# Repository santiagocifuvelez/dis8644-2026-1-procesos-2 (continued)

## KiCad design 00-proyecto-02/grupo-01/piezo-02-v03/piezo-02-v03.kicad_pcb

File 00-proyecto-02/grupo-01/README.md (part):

# proyecto-02

## Grupo

Número de grupo: 01

Tema del grupo: Piezo

Integrantes:

- Benjamín Alonso Álvarez Pavez / [benjaminalvarez21](<https://github.com/disenoUDP/dis8644-2026-1-procesos-2/tree/main/03-benjaminalvarez21>)
- Anays Valentina Cornejo Candia / [Anaysval](<https://github.com/disenoUDP/dis8644-2026-1-procesos-2/tree/main/09-Anaysval>)
- Bruno Ferrari Meyer / [chknngttts](<https://github.com/disenoUDP/dis8644-2026-1-procesos-2/tree/main/11-chknngttts>)
- Lucas Ignacio Ortiz Aguirre / [ryukivol](<https://github.com/disenoUDP/dis8644-2026-1-procesos-2/tree/main/21-ryukivol>)
- Nicolás Elías Valdés Greve / [nicolasvaldesgreve](<https://github.com/disenoUDP/dis8644-2026-1-procesos-2/tree/main/31-nicolasvaldesgreve>)

## Circuito 1

maincra

### Descripción general/conceptual 1

Este módulo te permite interactuar con el sintetizador mediante vibraciones en el piezo, tales como golpes en la misma superficie en la que se encuentra el componente o utilizándolo en nuestro cuerpo y causar vibraciones con nuestra garganta. Estas vibraciones serás captadas por el piezo, lo cual lo tomará como señal para avanzar en el secuenciador.

La idea detrás de esta propuesta nace de la posibilidad de sentir y ver las vibraciones. Aquello que parece caótico o insignificante puede contener señales que, al prestar suficiente atención, adquieren un significado propio. Siguiendo esa lógica, el piezo actúa como un medio para captar esas pequeñas vibraciones y convertirlas en acciones dentro del sintetizador, permitiendo que elementos normalmente invisibles se vuelvan parte de la interacción.

### Descripción de funcionamiento 1

El circuito se conforma de 7 partes:
  - Piezoeléctrico
  - Pre-Amp (TL072)
  - Inversor de señal (2N2222)
  - Regulador de voltaje (L7805CV)
  - Filtro Low-pass
  - Clock (NE555P)
  - Secuenciador (CD4017)

Como estándar en el trabajo todos tenemos que alimentar nuestro circuito con 5V. Para esto usamos el L7805CV

El piezo tiene 3 estados al recibir señal.

Para que el Pre-Amp pueda recibir la señal correctamente se necesita crear un voltaje medio entre VCC y GND. Para esto se usan 2 Resistencias del mismo valor, que dividen el voltaje a la mitad **``5V ---> 2.5V``**, esto permite que capte la señal completa y funcione correctamente. El Pre-Amp en nuestro caso también funciona para aumentar la sensibilidad del piezo, normalmente este solo detecta las señales directas al disco cerámico del piezo, pero con el Pre-Amp logramos que detecte señales a varios centímetros de este. 

Para afinar la señal que recibe el inversor, colocamos un filtro low-pass, esto permite que solo corriente bajo los 500hz *aprox.* avancen en el circuito. Esta señal entra al transistor (2N2222) que invierte la señal que recibe, puesto que el Clock (NE555P) busca recibir señales negativas en su Trigger [pin 2] para funcionar. El Clock en modo monoestable se conecta con el pin 14 del secuenciador (CD4017) para que señale cuando se avanza en los steps. 

### Descubrimientos

- Modificando los valores de las resistencias, se logra amplificar la sensibilidad del piezo (gracias misaaaaaa).
- Tener protoboard con los orificios **no** suelto es vital para que el circuito sea estable y se pueda mover.
- Que ciertos amplificadores tienen usos específicos, como el LM386 que es óptimo para parlantes, pero no piezos.
- Se pueden sustituir componentes con valores diferentes **``2.2k Ω ---> 47 Ω``**

### Esquemático 

### PCB 1

### Documentación audiovisual funcionamiento protoboard 1

[video-piezo-01](https://youtu.be/JZCzPmO_yxs)

### BOM

| Componente | Cantidad | Valor unitario | Link |
| --- | --- | --- | --- |
| Chip NE555P | 1 | $490 | <https://www.victronics.cl/circuitos-integrados/lm555cngeneralpurposebipolartimerdip8/> |
| Chip TL072CP | 1 | $990 | <https://www.victronics.cl/circuitos-integrados/tl072cpdualjfetlowpoweropamplifierdip8/> |
| Chip CD4017 | 1 | $890 | <https://www.mechatronicstore.cl/circuito-integrado-4017-contador/?srsltid=AfmBOopG29clQvJ0CqcNNp17wxEDjZ1w8dAWqRPMAcTqycciqYjHE40h>
| Regulador L7805CV | 1 | $350 | <https://www.victronics.cl/reguladores/reguladorvoltl7805cv5v-15ato220/> |
| Diodo 1N4007 | 1 | $200 | <https://www.mechatronicstore.cl/diodo-rectificador-in4007-1n4007-4007/> |
| Diodo BAT85 | 2 | $586 | <https://cl.rsdelivers.com/product/nexperia/bat85113/nexperia-diodo-bat85113-diodo-schottky-200-ma-30-v/0300978> |
| Transistor 2N2222 | 1 | $200 | <https://www.mechatronicstore.cl/transistor-2n2222/> |
| Potenciómetro B10K | 1 | $495 | <https://altronics.cl/potenciometro-lineal-10k-b10k> |
| Potenciómetro B500K | 1 | $495 | <https://altronics.cl/potenciometro-lineal-500k-b500k?search=b500k> |
| LED 3mm | 5 | $100 | <https://www.mechatronicstore.cl/led-3mm-5mm/> |
| Resistencia 47 Ω | 1 | $90 | <https://www.electroardu.cl/resistencias-1k-ohm?srsltid=AfmBOor81HKrzfoOTnLK3FU6ObPuf1EPUVMS0naCwqMNIzGt8LYDiUYt> |
| Resistencia 100 Ω | 1 | $90 | <https://www.electroardu.cl/resistencias-1k-ohm?srsltid=AfmBOor81HKrzfoOTnLK3FU6ObPuf1EPUVMS0naCwqMNIzGt8LYDiUYt> |
| Resistencia 220 Ω | 1 | $90 | <https://www.electroardu.cl/resistencias-1k-ohm?srsltid=AfmBOor81HKrzfoOTnLK3FU6ObPuf1EPUVMS0naCwqMNIzGt8LYDiUYt> |
| Resistencia 1 KΩ | 8 | $90 | <https://www.electroardu.cl/resistencias-1k-ohm?srsltid=AfmBOor81HKrzfoOTnLK3FU6ObPuf1EPUVMS0naCwqMNIzGt8LYDiUYt> |
| Resistencia 10 KΩ | 4 | $90 | <https://www.electroardu.cl/resistencias-1k-ohm?srsltid=AfmBOor81HKrzfoOTnLK3FU6ObPuf1EPUVMS0naCwqMNIzGt8LYDiUYt> |
| Resistencia 100 KΩ | 5 | $90 | <https://www.electroardu.cl/resistencias-1k-ohm?srsltid=AfmBOor81HKrzfoOTnLK3FU6ObPuf1EPUVMS0naCwqMNIzGt8LYDiUYt> |
| Condensador cerámico 4.7 nF | 1 | $100 | <https://www.mechatronicstore.cl/condensadores-ceramicos-distintos-valores/> |
| Condensador cerámico 10 nF | 1 | $100 | <https://www.mechatronicstore.cl/condensadores-ceramicos-distintos-valores/> |
| Condensador cerámico 100 nF | 4 | $100 | <https://www.mechatronicstore.cl/condensadores-ceramicos-distintos-valores/> |
| Condensador polarizado 10 µF | 2 | $100 | <https://www.mechatronicstore.cl/condensador-capacitorio-de-electrolitico-por-unidad-varios-valores/> |
| Condensador polarizado 100 µF | 3 | $100 | <https://www.mechatronicstore.cl/condensador-capacitorio-de-electrolitico-por-unidad-varios-valores/> | 
| Cables dupont 40 uni. | 1 | $2.990 | <https://mcielectronics.cl/shop/product/cable-dupont-macho-macho-20cm-pack-40-unidades-2/> |
| Cables caimán | 2 | $1.990 | <https://www.mechatronicstore.cl/cable-conector-cocodrilo-o-caiman-5-unidades/> |
| Batería 9V recargable | 1 | $7.990 | <https://www.sodimac.cl/sodimac-cl/articulo/110251085/bateria-recargable-9v/110251089> |
| Conector batería | 1 | $1.990 | <https://mcielectronics.cl/shop/product/conector-para-baterias-de-9v-9800/?srsltid=AfmBOorf4iqHmZZbBCSLCPoI-UFTBMuBMtXEwLw-ia48KteW5jir8sIx> |
| Piezo | 1 | $990 | <https://www.mechatronicstore.cl/sensor-piezoelectrico-27mm-con-cable/> |
| Interruptor Switch | 1 | $570 | <https://www.katode.cl/switches/1339-interruptor-switch-2-pines-on-off-corto.html?srsltid=AfmBOorJlIeUySzAORFwXSattHKE4BKH2LmhhXZS_8fZ4MW-G6kwnxqA> |

## Circuito 2

Budumtz

### Descripción general/conceptual 2

Este módulo, al igual que el anterior, permite que uno pueda interactuar con el sintetizador al que esté conectado el piezo, pero en este caso se necesita contacto directo al componente lo cual permitirá que lo que esté conectado a este se active.

El nombre surge de esos sonidos de batería cortos que suelen acompañar el remate de un chiste, donde un único golpe logra llamar la atención y marcar un momento específico.

De forma parecida, cada impacto sobre el piezo genera una respuesta inmediata en el circuito.

### Descripción de funcionamiento 2

El circuito se conforma por 5 partes:

+ Piezoeléctrico
+ High pass filter
+ Op-Amp (LM324)
+ Inversor de señal (2N2222)
+ Regulador de voltaje (L7805CV)

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
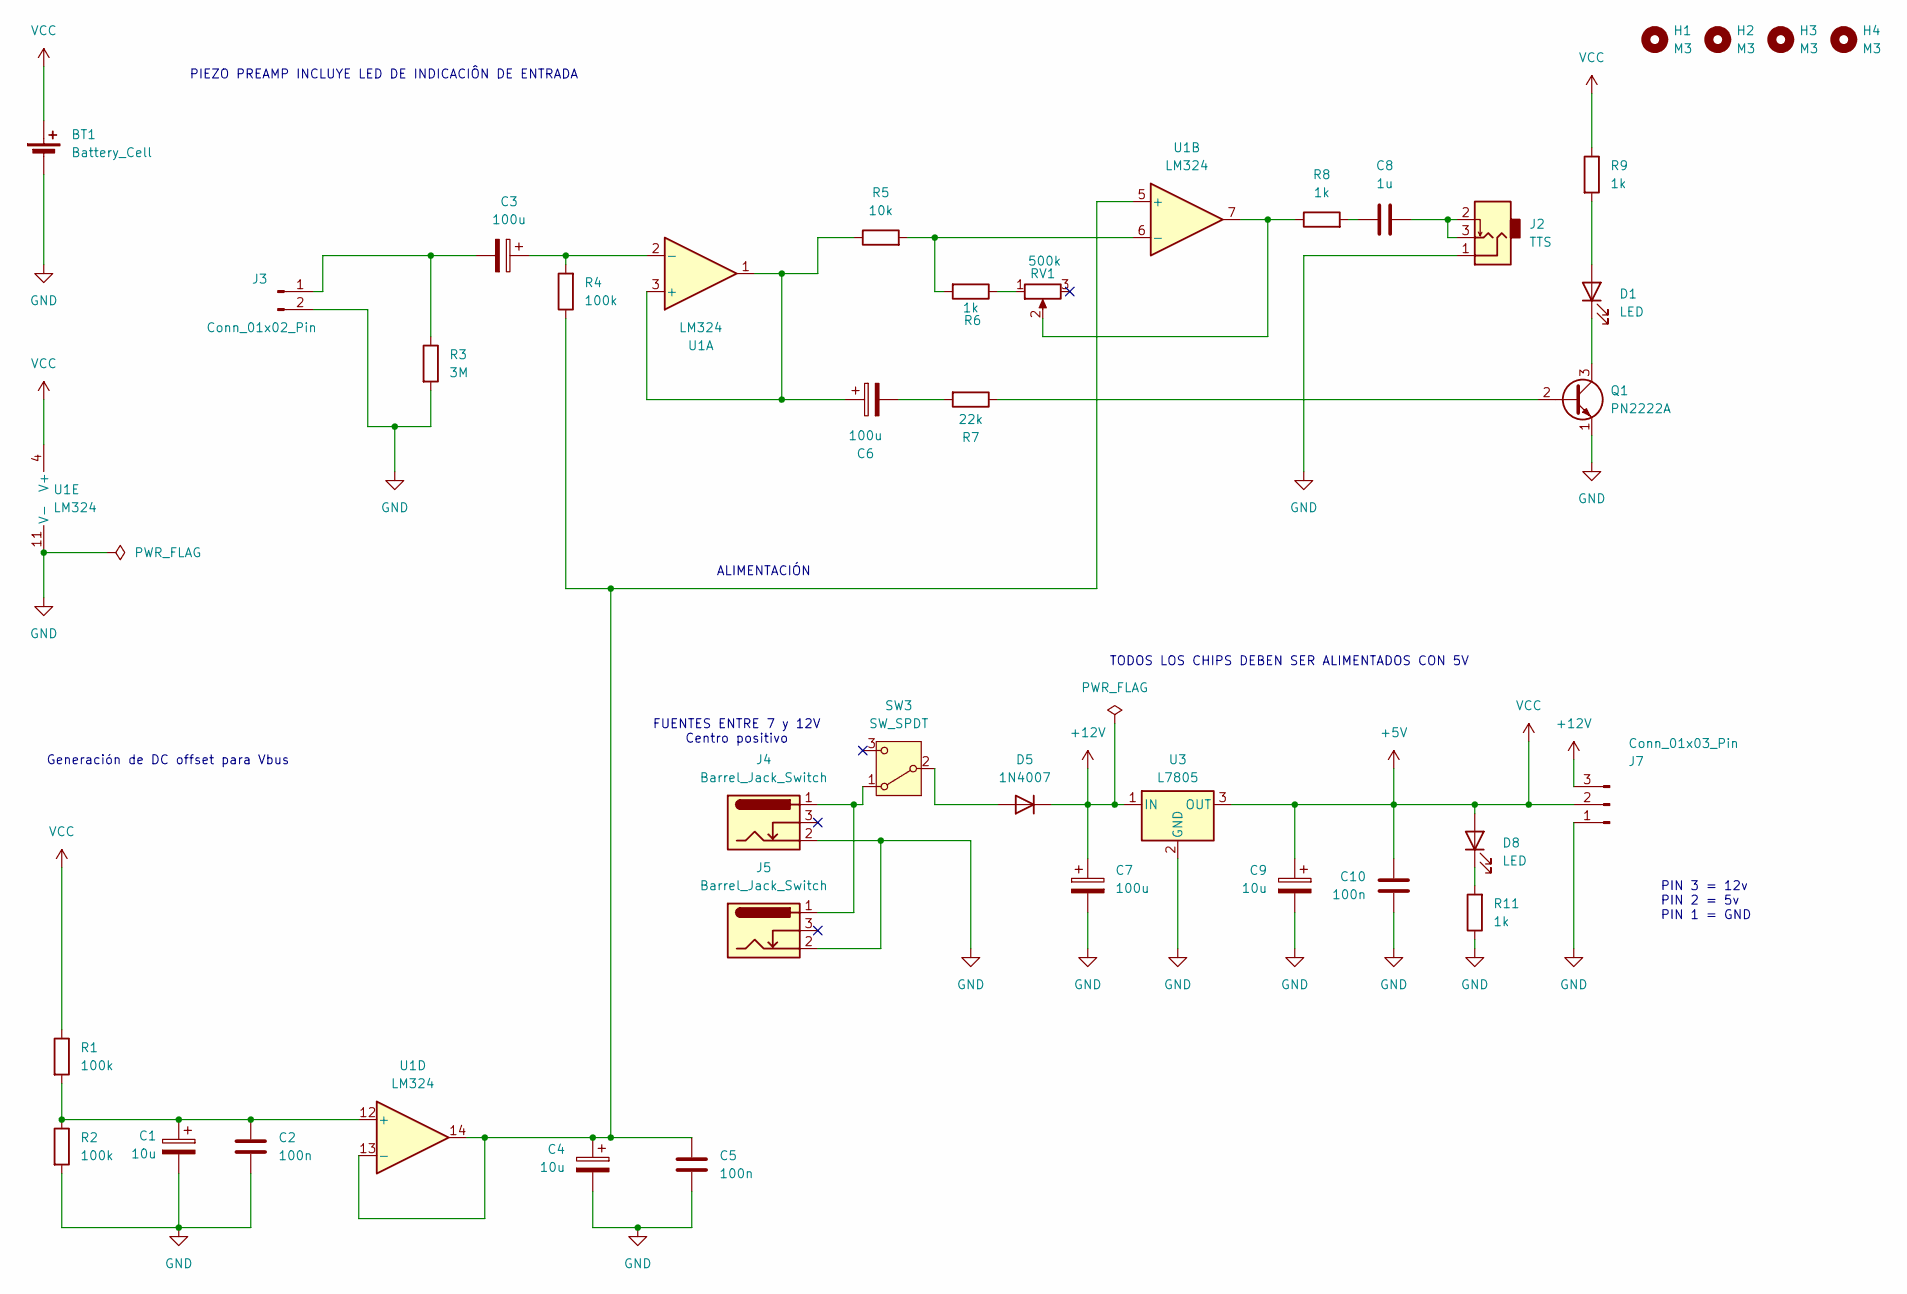
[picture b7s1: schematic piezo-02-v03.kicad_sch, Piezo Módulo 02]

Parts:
BT1: Battery_Cell; TerminalBlock_MaiXu_MX126-5.0-02P_1x02_P5.00mm
C1, C4, C9: 10u; CP_Radial_D4.0mm_P2.00mm
C2, C5, C10: 100n; C_Disc_D5.0mm_W2.5mm_P2.50mm
C3, C6, C7: 100u; CP_Radial_D8.0mm_P3.80mm
C8: 1u; C_Disc_D5.0mm_W2.5mm_P5.00mm
D1, D8: LED; LED_D5.0mm
D5: 1N4007; D_DO-41_SOD81_P10.16mm_Horizontal
H1, H2, H3, H4: M3; MountingHole_3.2mm_M3
J2: TTS; PJ301M-12
J3: Conn_01x02_Pin; PinSocket_1x02_P2.54mm_Vertical
J4, J5: Barrel_Jack_Switch; BarrelJack_Horizontal
J7: Conn_01x03_Pin; PinSocket_1x03_P2.54mm_Vertical
Q1: PN2222A; TO-92_Inline
R1, R2, R4: 100k; R_Axial_DIN0207_L6.3mm_D2.5mm_P10.16mm_Horizontal
R3: 3M; R_Axial_DIN0207_L6.3mm_D2.5mm_P10.16mm_Horizontal
R5: 10k; R_Axial_DIN0207_L6.3mm_D2.5mm_P10.16mm_Horizontal
R6, R8, R9, R11: 1k; R_Axial_DIN0207_L6.3mm_D2.5mm_P10.16mm_Horizontal
R7: 22k; R_Axial_DIN0207_L6.3mm_D2.5mm_P10.16mm_Horizontal
RV1: 500k; Potentiometer_Alps_RK163_Single_Horizontal
SW3: SW_SPDT; spdt_ssd12d00g3
U1: LM324; DIP-14_W7.62mm_LongPads
U3: L7805; TO-220-3_Vertical

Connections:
+5V: BT1.1 (+), C9.1, C10.1, D8.2 (A), J7.2, R1.1, R9.1, U1.4 (V+), U3.3 (OUT)
+12V: C7.1, D5.1 (K), J7.3, U3.1 (IN)
GND: BT1.2 (-), C1.2, C2.2, C4.2, C5.2, C7.2, C9.2, C10.2, J2.1, J3.2, J4.2, J5.2, J7.1, Q1.1 (E), R2.2, R3.2, R11.1, U1.11 (V-), U3.2 (GND)
unnamed: C6.2, R7.2
unnamed: C8.1, R8.2
unnamed: C8.2, J2.2, J2.3
unnamed: D1.2 (A), R9.2
unnamed: D1.1 (K), Q1.3 (C)
unnamed: D5.2 (A), SW3.2 (B)
unnamed: D8.1 (K), R11.2
unnamed: C3.2, J3.1, R3.1
unnamed: Q1.2 (B), R7.1
unnamed: R6.1, RV1.1
unnamed: R8.1, RV1.2, U1.7
unnamed: J4.1, J5.1, SW3.1 (A)
unnamed: C6.1, R5.1, U1.1, U1.3 (+)
unnamed: C3.1, R4.2, U1.2 (-)
unnamed: C4.1, C5.1, R4.1, U1.5 (+), U1.13 (-), U1.14
unnamed: R5.2, R6.2, U1.6 (-)
unnamed: C1.1, C2.1, R1.2, R2.1, U1.12 (+)

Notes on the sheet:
TODOS LOS CHIPS DEBEN SER ALIMENTADOS CON 5V
PIEZO PREAMP INCLUYE LED DE INDICACIÔN DE ENTRADA
FUENTES ENTRE 7 y 12V Centro positivo
ALIMENTACIÓN
PIN 3 = 12v PIN 2 = 5v PIN 1 = GND
Generación de DC offset para Vbus

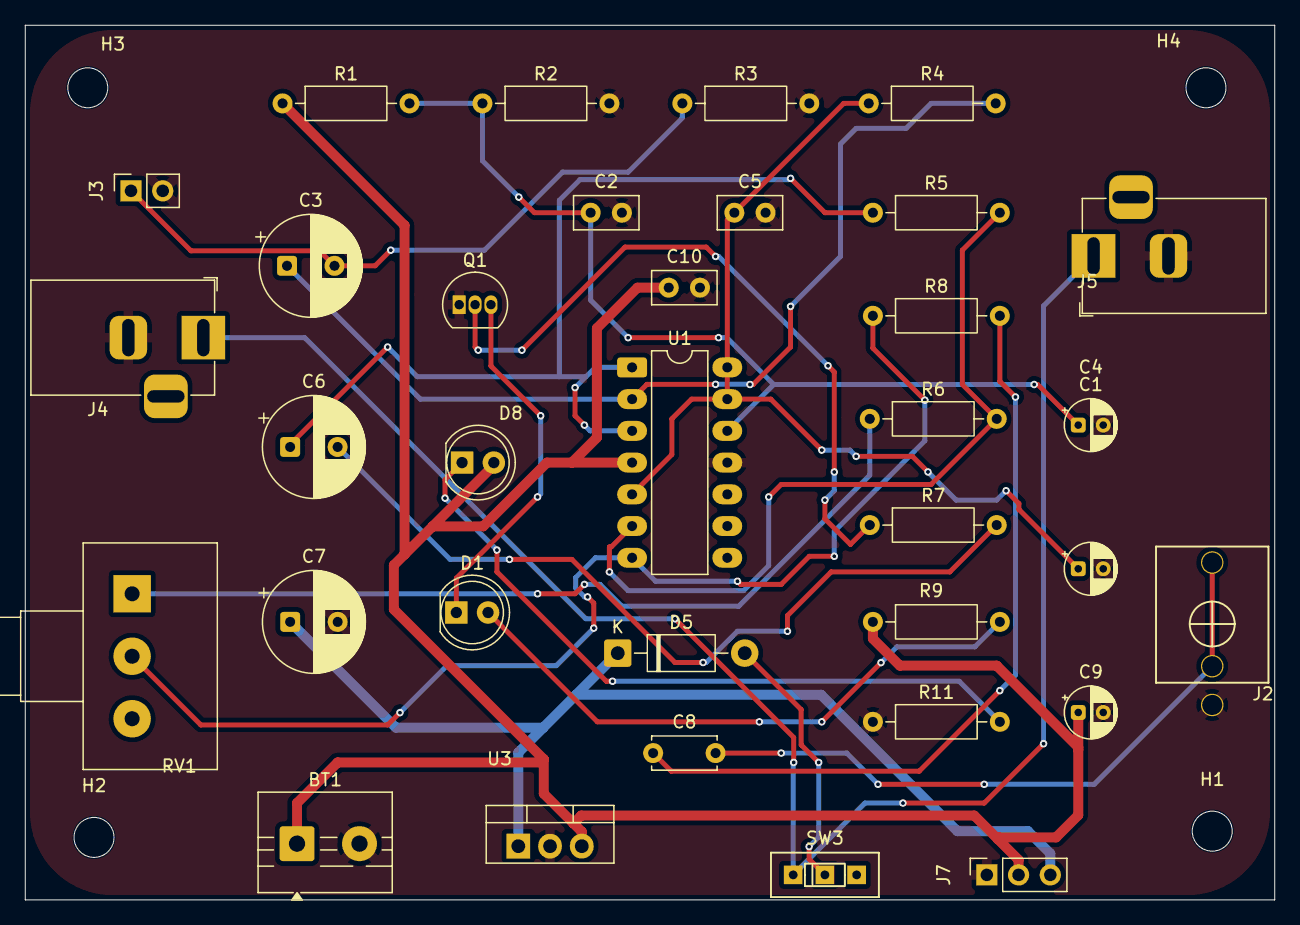
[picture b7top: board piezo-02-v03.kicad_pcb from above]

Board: 2 copper layers, 100.0 x 70.0 mm, 38 parts (0 on the bottom side), 20 nets.

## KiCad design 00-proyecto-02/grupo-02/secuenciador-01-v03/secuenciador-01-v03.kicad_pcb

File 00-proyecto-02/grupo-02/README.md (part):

# proyecto-02

## Grupo

Número de grupo: 02

Tema del grupo: Secuenciador 

Integrantes:

- Isidora Alvarez / 
- Dayana Pañitrur / dayanapanitrur
- Camila Ramirez / Estrabismx
- Angel Sabogal / angel-udp
- Tomas Catrileo / tomascatri
  
## Circuito 1: Contador binario

### Descripción general/conceptual 1

Este circuito es un compás, es decir que le da ritmo a lo que pueda sonar, ya que esté no define ninguna nota, simplemente el ritmo y en este caso uno donde tenemos 6 compases, cada uno a un ritmo diferente

Es bastante autónomo, solamente debes indicarle que _partitura_ va a interpretar cada compás y solito hará su trabajo

<br>

### Descripción de funcionamiento 1

Ahora se van a definir algunos conceptos claves:

Podemos categorizarlo como un secuenciador, es decir que genera corrientes eléctricas en un patrón repetitivo y ordenado. Un ejemplo de esto es un semáforo, ya que se va a prender siempre en el mismo orden:

_VERDE > AMARILLO > ROJO > VERDE > AMARILLO > ROJO > ..._

<br>

Ya definimos que este sistema es un secuenciador, pero algo importante es como está configurada la duración de cada _activación_. Tal como en los semáforos no todos los colores duran lo mismo, en este circuito cada _señal_ tiene una duración única. ¿A que se refiere "duración unica"? En que cada _señal_ está asociada a un número, desde el 0 al 12 y mientras menor sea el número asociado, más rapido se va a _activar_. A continuación se puede observar una representación de este patrón

> De izquierda a derecha: Avance del tiempo
>
> De arriba a abajo: Q1, Q2, Q3, Q4 y Q5 = Canales

<br>

Esta es una secuencia binaria y de las cosas más notorias es que cada _canal_ tiene la misma duración prendido y apagado, es decir, el Q3 funciona con 4 _señales apagadas_ y 4 _señales prendidas_. Otro punto interesante es como esta duración tambien sigue un patrón

| Canal / Step | Duración   |
| ------------ | ---------- |
| Q1           | 1 tiempo   |
| Q2           | 2 tiempos  |
| Q3           | 4 tiempos  |
| Q4           | 8 tiempos  |
| Q5           | 16 tiempos |

<br>

Ahora que entendemos como funciona su secuencia, vamos a profundizar más en como este circuito logra generar este proceso. Anteriormente se mencionó (y tmabien se ejemplificó en la imagen) que en cada _"tiempo"_ se van _activando_ las señales correspondientes, estos "_tiempos_" son corrientes eléctricas, es decir, que se necesita una señal intermitente y constante para activar el proceso de conteo. Esto es conocido como **reloj** o **clock**, entonces la velocidad con la que alterne este circuito afectará en como nuestro secuenciador realice su conteo.

Para una mayor compresión se utilizará la siguiente analogía: Tenemos una especie de corazón (Reloj) que cada vez que late (emitir un pulso eléctrico) un semáforo prende sus luces (se activan las salidas del secuenciador)

Otro ejemplo que nos puede ayudar a entender como funciona es que cada Q es un corredor en una carrera con saltos.

El corredor del carril Q0 va a correr un metro y debe saltar un metro, luego correr un metro y volver a saltar otro, asi sucesivamente. El del carril Q1 debera correr por 2 metros y sus saltos tambien deberán ser de 2 metros. Quien tenga la mala suerte de correr en el Q2, tendrá que hacerlo por 4 metros y saltar tambien 4 de ellos.

Todos ellos van a iniciar al mismo tiempo, eventualmente veremos que sus saltos se coordinan cada ciertos metros

>Clickear imagen para reproducir video

#### Explicación más técnica

Ahora con otro tipo de explicación, debemos entender que el cerebro detrás de todo este sistema es un chip CD4040, el cual recibe un **input** intermitente (en nuestro caso de prueba un reloj en base a un CD555 Astable), cada vez que se reciba una señal el contador iniciará. Recordemos que acá no se cuenta con otro número que no sea 0 y 1. Al cambiar el conteo se van a producir 2 cosas importantes:

1. Se prenderá un led corresponiente al conteo

2. Se activará el **output** que corresponda

Por lo que cada vez que se envie una señal en cada paso, se prenderá un respectivo led, ya que todo es más facil de entender cuando vemos (además nos puede ayudar a identificar donde puede haber un problema). El como se prende este led es simple, utilizamos un transistor del tipo NPN, más especificamente un 2N2222, este funciona como un interruptor, cada vez que el IC manda una señal este transistor permite el paso de la corriente del led. Profundizando esto hay que entender que el led está conectado a VCC (con su respectiva resistencia), luego se conecta al colector del 2N2222 y el emisor a Ground, por lo que cuando la base de este reciba señal va a permitir que se cierre el circuito del led. En resumen, este transistor no es más que un switch inteligente.

Algo importante a mencionar es la alimentación de este IC, este recibe 5v gracias al regulador de voltaje (L7805)

### Proceso

Para el proyecto tuvimos diferentes etapas: iniciamos con un proceso de investigación individual para obtener variadas opciones de chips o formas de lograr un secuenciador y compararlas de manera grupal. Viendo entre varias opciones que nos dio internet, existían algunas que nos llamaban más la atención que otras. Como grupo vimos hasta la posibilidad de no usar chip, pero creímos que sería un desafío mucho mayor sin aún comprender muy bien cómo funcionaban los transistores, además de que, si bien pueden lograr hacer cosas similares a los circuitos integrados, ya que estos básicamente están compuestos por una gran cantidad de transistores y muchos componentes más pero de una forma más compacta, podría resultar más inestable, se requeriría un espacio muchísimo mayor para colocar una gran cantidad de componentes y por último y como ya se mencionó, un chip hace lo mismo en un espacio, tiempo y trabajo menor. Después de mucha indecisión y de ver cuál de estas opciones eran viables e interesantes, llegamos a la conclusión de usar los circuitos integrados CD4040 y CD4015, ya que estos nos permiten generar secuencias de manera distinta, igual nos aventuramos en elegir estos chips ya que nunca lo habíamos visto y eran circuitos que encontramos en internet y no sabíamos si lograriamos hacerlo, aceptamos el desafío y fui a san diego por suministros de chips.

Empezamos hacer las primeras pruebas utilizamos el CD555, que se encarga de generar los pulsos que controlan la manera en cómo avanza el secuenciador, durante esta etapa surgieron distintos problemas, tuvimos fallas con conexiones, errores de cableado y componentes defectuosos, íbamos registrando y corrigiendo en el acto para no perdernos, esto nos permitió mejorar el funcionamiento, generar hipótesis de los posibles errores y adelantarnos a posibles fallas.

Con el CD4040 hicimos varias pruebas para ver que funcionara bien el contador binario es decir un contador de pulsos o pasos cada vez que recibe una señal,  permitiendo generar secuencias y patrones de activación, también podemos imaginarlo como si fuera las luces de un árbol de navidad, algunas luces se prenden, otras se apagan y van formando distintos dibujos,  es decir cada vez que el circuito recibe una señal cambia el patrón de luces, creando nuevas combinaciones. Comenzamos utilizando pocas salidas y a medida que veíamos que iba funcionando le íbamos agregando más leds, para poder observar mejor la secuencia que se generaba, tuvimos fallas con la batería, conexiones a negativo (tierra) que no habíamos puesto, se nos quemaron algunos leds para variar. Cuando logramos hacer que todo esté bien conectado y arreglar todos los problemas, logramos que funcionara de manera estable, vimos cómo se comportaba y funcionaba el chip, y como son los pulsos que tiene el chip.
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
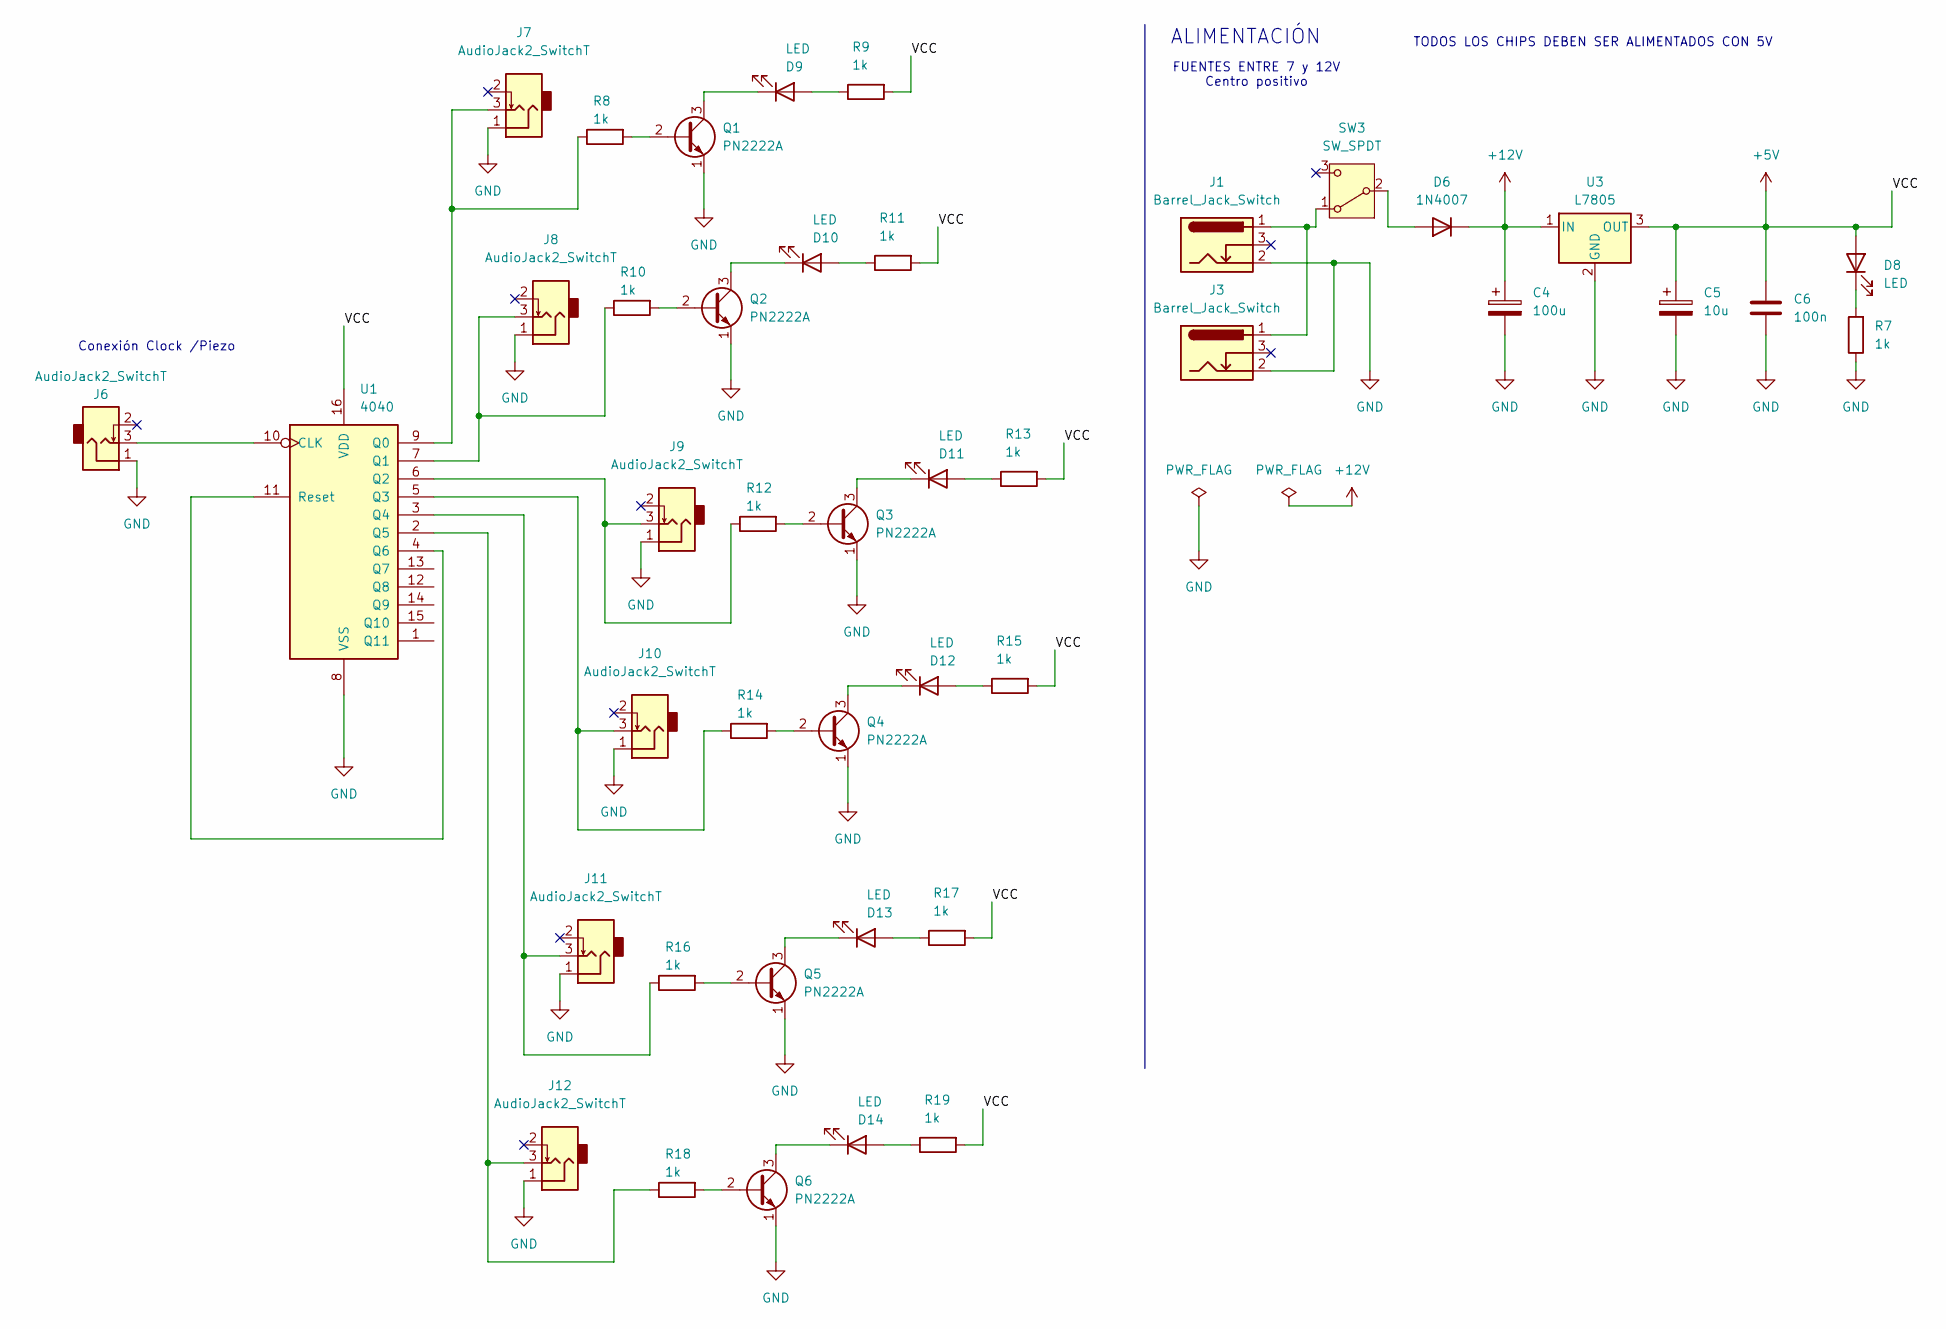
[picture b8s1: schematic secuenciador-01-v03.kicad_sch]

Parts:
C4: 100u; CP_Radial_D8.0mm_P3.80mm
C5: 10u; CP_Radial_D4.0mm_P2.00mm
C6: 100n; C_Disc_D5.0mm_W2.5mm_P2.50mm
D6: 1N4007; D_DO-41_SOD81_P10.16mm_Horizontal
D8, D9, D10, D11, D12, D13, D14: LED; LED_D5.0mm
J1, J3: Barrel_Jack_Switch; BarrelJack_Horizontal
J6, J7, J8, J9, J10, J11, J12: AudioJack2_SwitchT; PJ301M-12
Q1, Q2, Q3, Q4, Q5, Q6: PN2222A; TO-92_Inline
R7, R8, R9, R10, R11, R12, R13, R14, R15, R16, R17, R18, R19: 1k; R_Axial_DIN0207_L6.3mm_D2.5mm_P10.16mm_Horizontal
SW3: SW_SPDT; spdt_ssd12d00g3
U1: 4040; DIP-16_W7.62mm
U3: L7805; TO-220-3_Horizontal_TabDown

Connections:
+5V: C5.1, C6.1, D8.2 (A), R9.2, R11.2, R13.2, R15.2, R17.2, R19.2, U1.16 (VDD), U3.3 (OUT)
+12V: C4.1, D6.1 (K), U3.1 (IN)
GND: C4.2, C5.2, C6.2, J1.2, J3.2, J6.1, J7.1, J8.1, J9.1, J10.1, J11.1, J12.1, Q1.1 (E), Q2.1 (E), Q3.1 (E), Q4.1 (E), Q5.1 (E), Q6.1 (E), R7.1, U1.8 (VSS), U3.2 (GND)
unnamed: D6.2 (A), SW3.2 (B)
unnamed: D8.1 (K), R7.2
unnamed: D9.2 (A), R9.1
unnamed: D9.1 (K), Q1.3 (C)
unnamed: D10.2 (A), R11.1
unnamed: D10.1 (K), Q2.3 (C)
unnamed: D11.2 (A), R13.1
unnamed: D11.1 (K), Q3.3 (C)
unnamed: D12.2 (A), R15.1
unnamed: D12.1 (K), Q4.3 (C)
unnamed: D13.2 (A), R17.1
unnamed: D13.1 (K), Q5.3 (C)
unnamed: D14.2 (A), R19.1
unnamed: D14.1 (K), Q6.3 (C)
unnamed: Q1.2 (B), R8.2
unnamed: Q2.2 (B), R10.2
unnamed: Q3.2 (B), R12.2
unnamed: Q4.2 (B), R14.2
unnamed: Q5.2 (B), R16.2
unnamed: Q6.2 (B), R18.2
unnamed: J1.1, J3.1, SW3.1 (A)
unnamed: J6.3, U1.10 (CLK)
unnamed: J7.3, R8.1, U1.9 (Q0)
unnamed: J8.3, R10.1, U1.7 (Q1)
unnamed: J9.3, R12.1, U1.6 (Q2)
unnamed: J10.3, R14.1, U1.5 (Q3)
unnamed: J11.3, R16.1, U1.3 (Q4)
unnamed: J12.3, R18.1, U1.2 (Q5)
unnamed: U1.4 (Q6), U1.11 (Reset)

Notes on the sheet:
Conexión Clock /Piezo
ALIMENTACIÓN
FUENTES ENTRE 7 y 12V Centro positivo
TODOS LOS CHIPS DEBEN SER ALIMENTADOS CON 5V

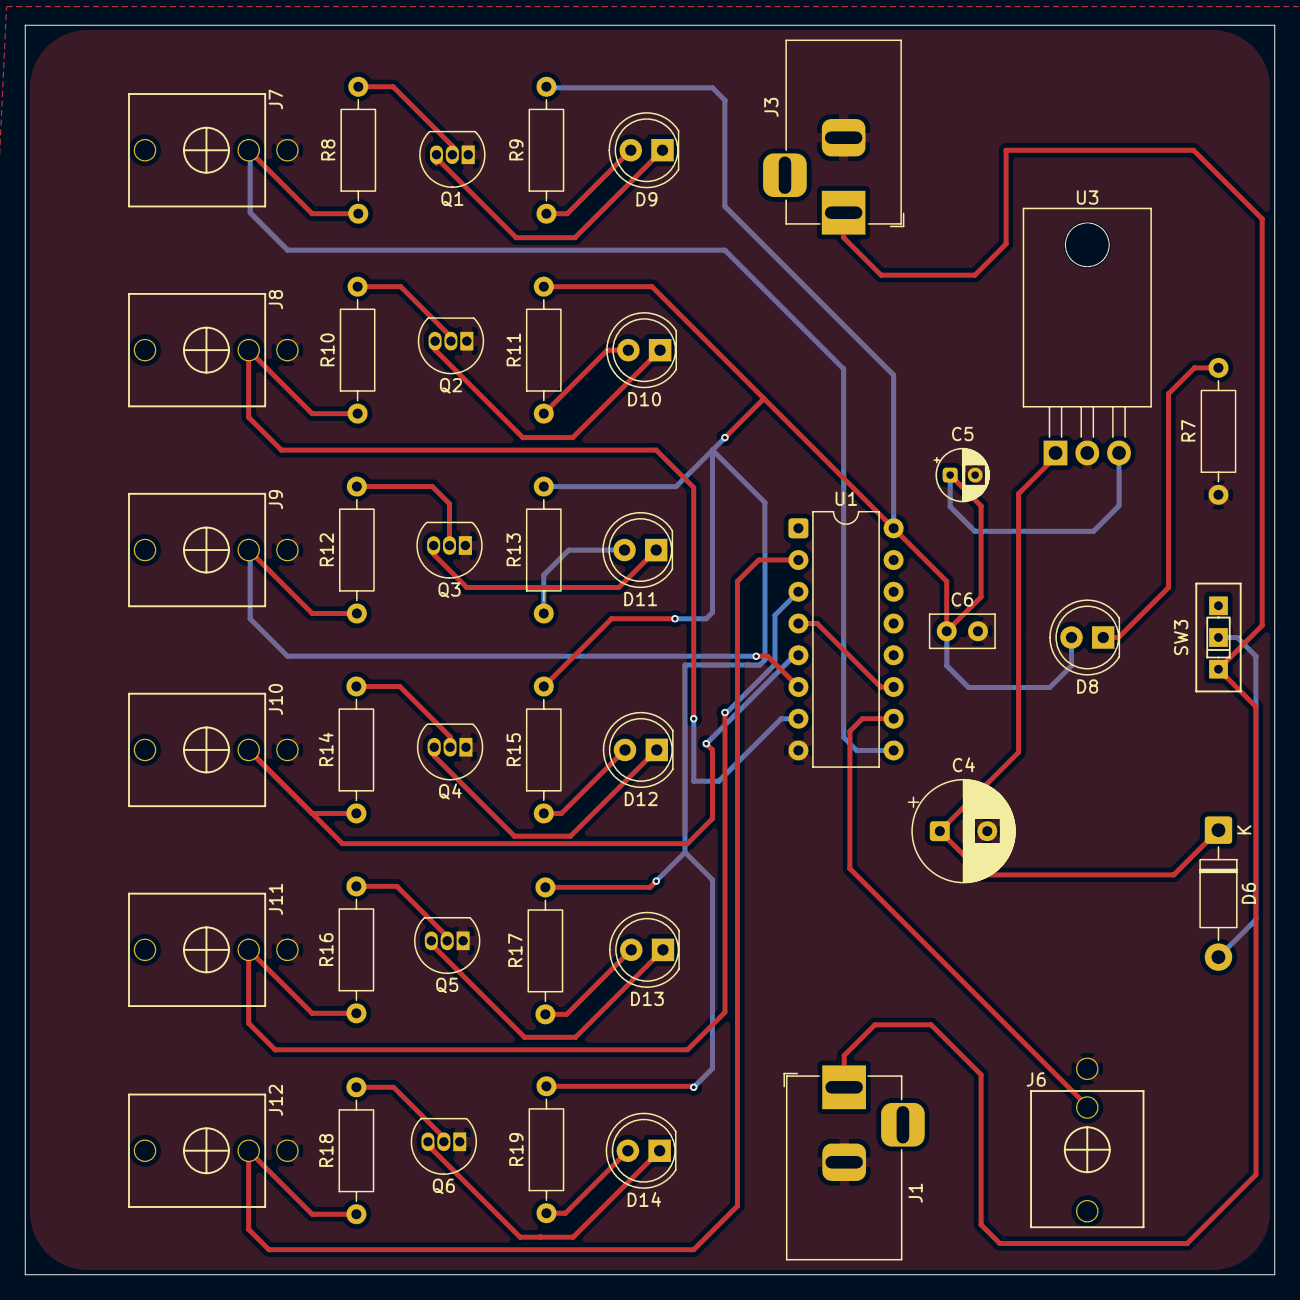
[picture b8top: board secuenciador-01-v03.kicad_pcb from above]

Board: 2 copper layers, 100.0 x 100.0 mm, 42 parts (0 on the bottom side), 32 nets.

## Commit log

2026-05-15 Rename imagen4.Ppng to imagen4.png
2026-05-15 agregar README
2026-05-18 placa555
2026-05-18 Add placa555 image to README
2026-05-18 Add more images to README.md
    Added additional images to the README file.
2026-05-19 Fix section title and enhance PCB Editor instructions
    Corrected section title and improved clarity in instructions.
2026-05-21 fotos resultados placa
2026-05-21 Add image of 'pizarra de misa' to README
    Added an image to the README file to enhance content.
2026-05-22 sesion-in-correcta
2026-05-25 Clase martes 12 de mayo.md
2026-05-25 agrego punteo libro
2026-05-26 Rename avance3.PNG to avance3.png
2026-05-26 eliminar archivo borrar
2026-05-26 Rename Captura de pantalla 2026-05-26 095021.png to CD4015.png
2026-06-02 Expand README with PCB and KiCad details
    Added detailed notes on PCBs, buttons, KiCad symbol editing, and photography concepts.
2026-06-02 Enhance README with session 10a notes and insights
    Added detailed notes on session 10a covering discussions on measurement, voltage concepts, and photography comparisons. Included insights from a talk and various technical explanations.
2026-06-02 agregar a 11b
2026-06-03 cambiar-carpeta
2026-06-03 arreglos-11b
2026-06-03 Rename piezo-02-v03_pro.kicad_pro to piezo-02-v03.kicad_pro
2026-06-03 agregar
2026-06-03 mover a carpetas
2026-06-03 Rename Captura de pantalla 2026-06-03 193757.png to secuenciador-4040.png
2026-06-04 esq-malo
2026-06-05 Create esquematicos
2026-06-05 pcb-imagen-video
2026-06-05 Rename image (1).png to pcb-back-2.png
2026-06-05 fotos-agregadas.md
2026-06-06 crear carpeta
2026-06-06 borrar README extra
2026-06-06 agregar archivos renombrados
2026-06-06 actualizar guiones
2026-06-06 borrar archivos extra
2026-06-09 foto-faltante
2026-06-09 agregar carpetas con README en blanco
2026-06-12 agrego imagenes
2026-06-14 Add introduction to schematics and revise reflection
    Updated the README.md to include an introduction to schematics in KiCad and revised the personal reflection on learning the software.
2026-06-14 agregar apuntes paula
2026-06-14 Update README with project 02 presentation info
    Added project presentation details and images.
2026-06-16 agrego info clase
2026-06-17 Fix typo in README.md regarding 'diarre' to 'diarrea'
2026-06-18 agrego ss
2026-06-19 links
    Updated the README.md file to include project details, materials list, assembly instructions, and visual score references.
2026-06-19 Update README.md with group details and materials
2026-06-22 Update README with corrections and project details
    Corrected grammar and added clarification about project integration.
2026-06-22 Rename Captura de pantalla 2026-06-21 213730.png to yoko-ono-02.png
2026-06-23 agrego ss libro
